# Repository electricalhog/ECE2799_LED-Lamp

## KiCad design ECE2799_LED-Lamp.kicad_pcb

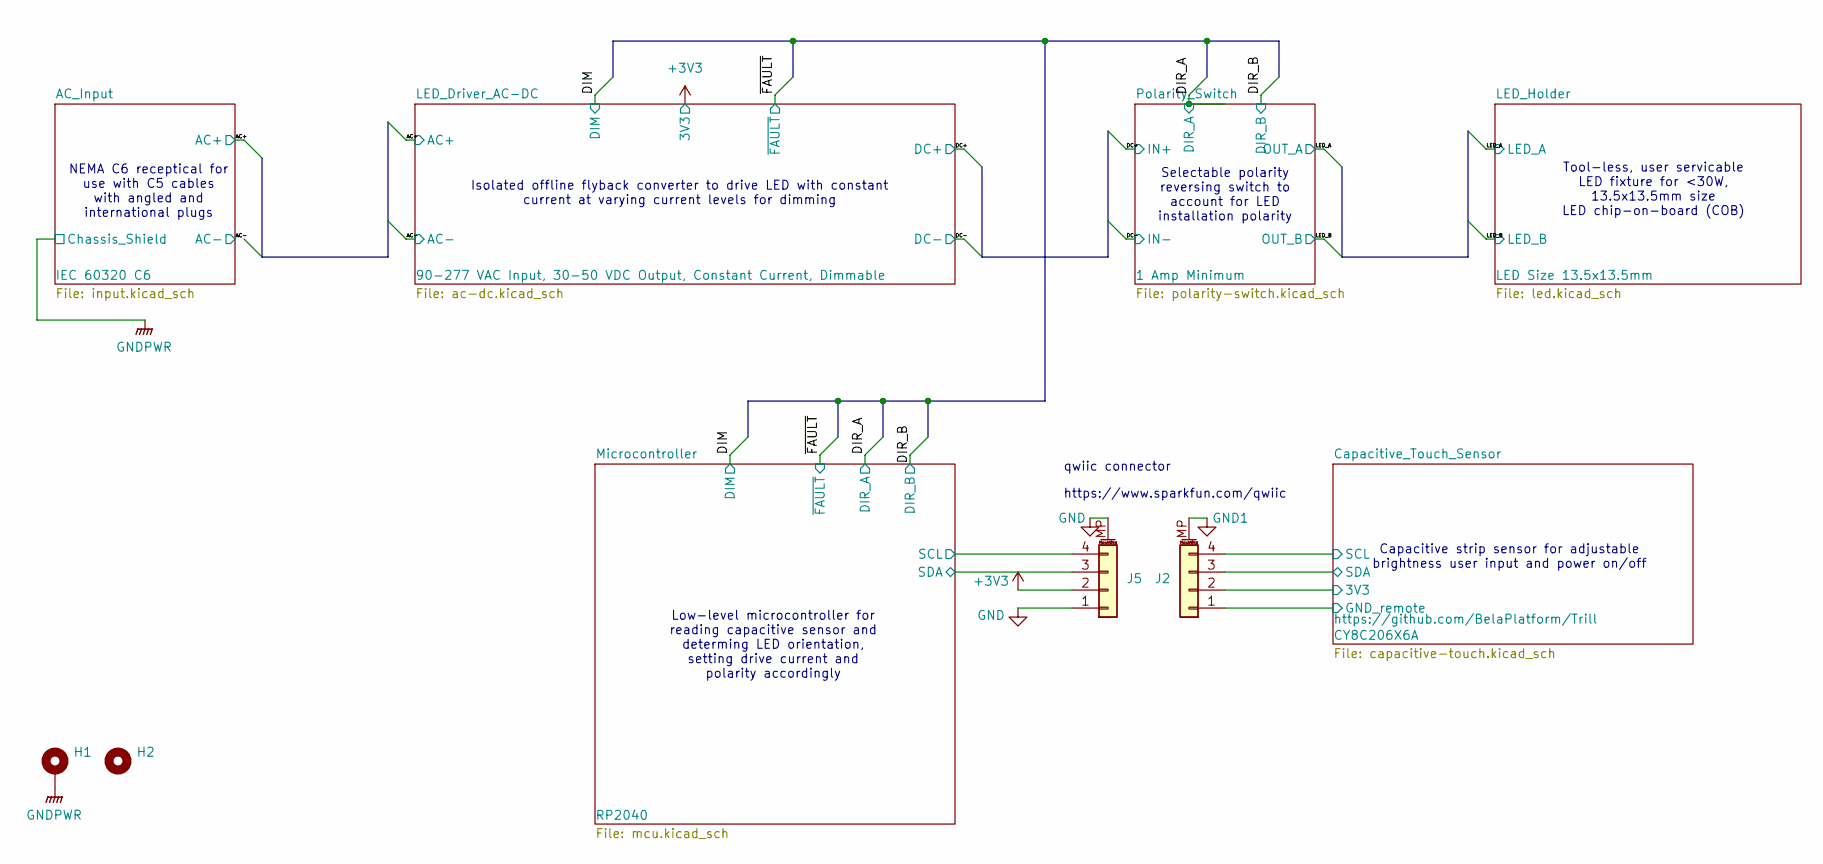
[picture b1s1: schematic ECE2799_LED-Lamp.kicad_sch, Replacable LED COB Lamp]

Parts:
H1: MountingHole_Pad; MountingHole_3.2mm_M3_Pad
H2: MountingHole; MountingHole_3.2mm_M3
J2, J5: Conn_01x04_MountingPin; qwiic_horizontal_SMD; Part Number PRT-14417-ND

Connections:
+3V3: J5.2; also elsewhere on the board
/Capacitive_Touch_Sensor/SCL: J2.4; also elsewhere on the board
/Capacitive_Touch_Sensor/SDA: J2.3; also elsewhere on the board
/Microcontroller/SCL: J5.4; also elsewhere on the board
/Microcontroller/SDA: J5.3; also elsewhere on the board
GND: J5.1, J5.MP (MountPin); also elsewhere on the board
GND1: J2.1, J2.MP (MountPin); also elsewhere on the board
GNDPWR: H1.1; also elsewhere on the board
VCC: J2.2; also elsewhere on the board

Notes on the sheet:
https://www.sparkfun.com/qwiic
NEMA C6 receptical for use with C5 cables with angled and international plugs
Isolated offline flyback converter to drive LED with constant current at varying current levels for dimming
Selectable polarity reversing switch to account for LED installation polarity
Tool-less, user servicable LED fixture for <30W, 13.5x13.5mm size LED chip-on-board (COB)
Low-level microcontroller for reading capacitive sensor and determing LED orientation, setting drive current and polarity accordingly
Capacitive strip sensor for adjustable brightness user input and power on/off
qwiic connector

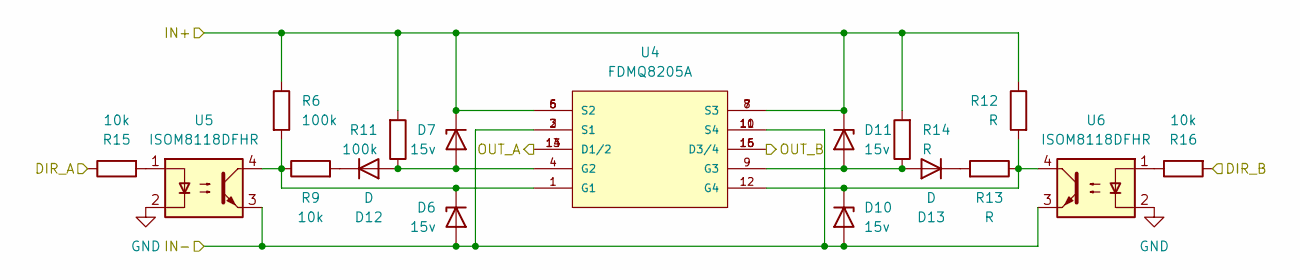
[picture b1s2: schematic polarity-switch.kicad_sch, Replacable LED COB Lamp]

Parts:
D6, D7, D10, D11: 15v; D_0603_1608Metric; Part Number 1727-6235-1-ND
D12, D13: D; D_0603_1608Metric; Part Number 1N4148WTDICT-ND
R6, R11: 100k; R_0603_1608Metric
R9, R15, R16: 10k; R_0603_1608Metric
R12, R13, R14: R; R_0603_1608Metric
U4: FDMQ8205A; IC_FDMQ8205A; PARTREV 1.0
U5, U6: ISOM8118DFHR; SOP-4_4.4x2.6mm_P1.27mm; Part Number 296-ISOM8118DFHRCT-ND

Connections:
/DC+: D7.1 (K), D11.1 (K), R6.1, R11.2, R12.1, R14.2, U4.5 (S2), U4.6 (S2), U4.7 (S3), U4.8 (S3); also elsewhere on the board
/DC-: D6.2 (A), D10.2 (A), U4.2 (S1), U4.3 (S1), U4.10 (S4), U4.11 (S4), U5.3, U6.3; also elsewhere on the board
/DIR_A: R15.1; also elsewhere on the board
/DIR_B: R16.2; also elsewhere on the board
/LED_A: U4.13 (D1/2), U4.14 (D1/2); also elsewhere on the board
/LED_B: U4.15 (D3/4), U4.16 (D3/4); also elsewhere on the board
GND: U5.2, U6.2; also elsewhere on the board
unnamed: D6.1 (K), R6.2, R9.1, U4.1 (G1), U5.4
unnamed: D10.1 (K), R12.2, R13.1, U4.12 (G4), U6.4
unnamed: D11.2 (A), D13.2 (A), R14.1, U4.9 (G3)
unnamed: D7.2 (A), D12.2 (A), R11.1, U4.4 (G2)
unnamed: D12.1 (K), R9.2
unnamed: D13.1 (K), R13.2
unnamed: R15.2, U5.1
unnamed: R16.1, U6.1

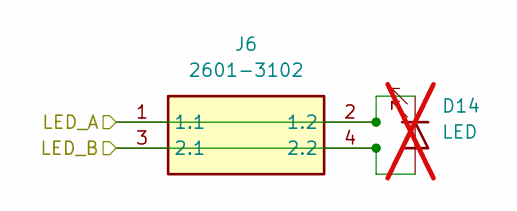
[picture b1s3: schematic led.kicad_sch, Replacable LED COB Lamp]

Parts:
D14: LED; Part Number 976-BXRH-40H1000-B-83-ND; not fitted
J6: 2601-3102; 26013102; Manufacturer_Part_Number 2601-3102

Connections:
/LED_A: D14.1 (K), J6.1 (1.1), J6.2 (1.2); also elsewhere on the board
/LED_B: D14.2 (A), J6.3 (2.1), J6.4 (2.2); also elsewhere on the board

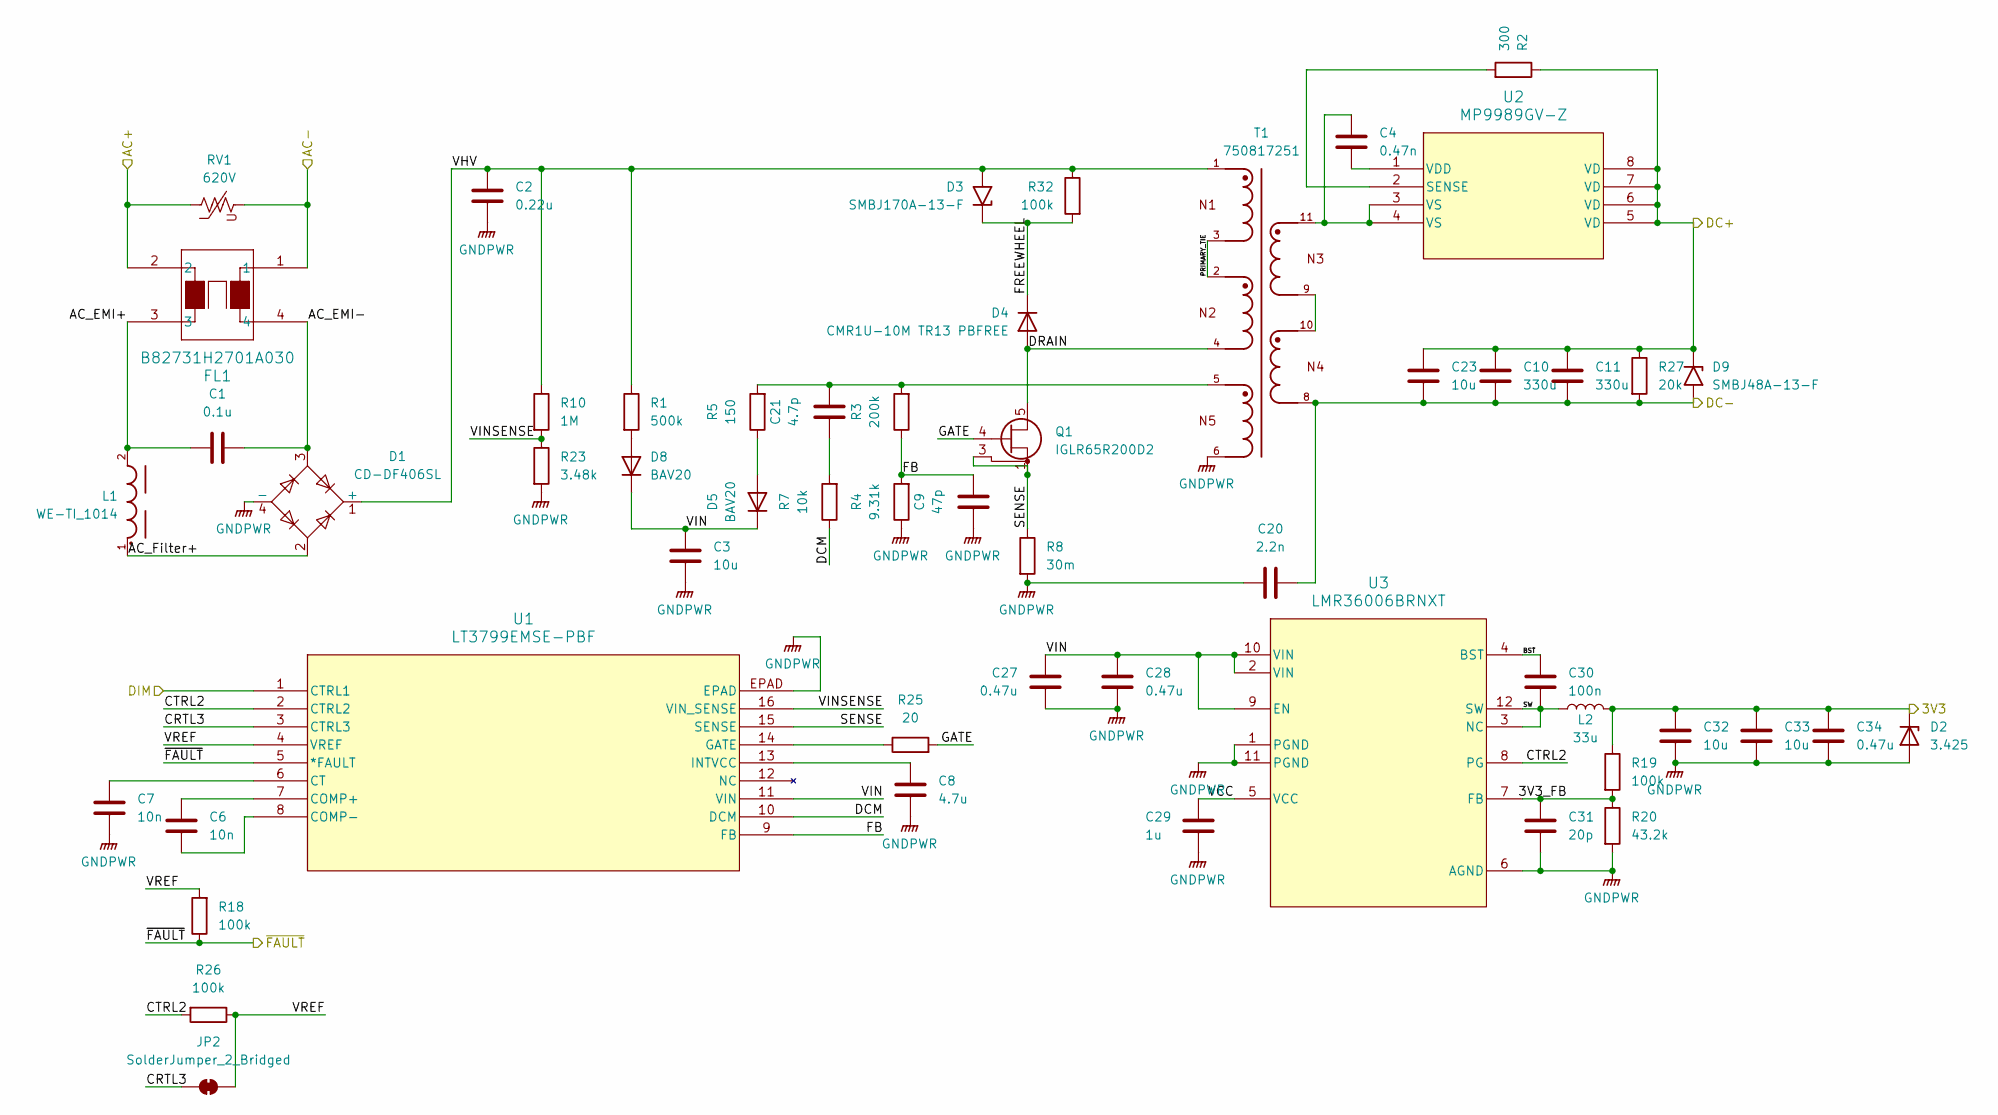
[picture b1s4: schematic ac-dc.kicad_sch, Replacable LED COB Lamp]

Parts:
C1: 0.1u; C_Rect_L13.0mm_W8.0mm_P10.00mm_FKS3_FKP3_MKS4; Part Number 732-5733-ND
C2: 0.22u; C_Rect_L18.0mm_W9.0mm_P15.00mm_FKS3_FKP3; Part Number 732-890414025003CS-ND
C3: 10u; CP_Radial_D5.0mm_P2.00mm; Part Number 732-9289-1-ND
C4: 0.47n; C_0603_1608Metric
C6, C7: 10n; C_0603_1608Metric
C8: 4.7u; C_0603_1608Metric
C9: 47p; C_0603_1608Metric
C10, C11: 330u; CP_Radial_D12.5mm_P5.00mm; Part Number UBT1J331MHD8-ND
C20: 2.2n; C_Disc_D11.0mm_W5.0mm_P10.00mm; Part Number BC3229-ND
C21: 4.7p; C_0603_1608Metric
C23, C32, C33: 10u; C_1206_3216Metric; Part Number 1276-6767-1-ND
C27, C28, C34: 0.47u; C_0805_2012Metric; Part Number 1276-6482-1-ND
C29: 1u; C_0603_1608Metric
C30: 100n; C_0603_1608Metric
C31: 20p; C_0603_1608Metric
D1: CD-DF406SL; Diode_Bridge_Bourns_CD-DF4xxS; Part Number 118-CD-DF406SLCT-ND
D2: 3.425; D_0603_1608Metric; Part Number 1727-8343-1-ND
D3: SMBJ170A-13-F; D_SMB; Part Number 31-SMBJ170A-13-FCT-ND
D4: CMR1U-10M TR13 PBFREE; D_SMA; Part Number 1514-CMR1U-10MTR13PBFREECT-ND
D5, D8: BAV20; D_SOD-123; Part Number BAV20W-FDICT-ND
D9: SMBJ48A-13-F; D_SMB; Part Number SMBJ48A-FDICT-ND
FL1: B82731H2701A030; B82731H_EPC; Part Number 495-5744-ND
JP2: SolderJumper_2_Bridged; SolderJumper-2_P1.3mm_Bridged2Bar_RoundedPad1.0x1.5mm
L1: WE-TI_1014; Part Number 732-4199-ND
L2: 33u; L_Wuerth_MAPI-3015; Part Number 732-4871-1-ND
Q1: IGLR65R200D2; PG-TSON-8-8; Part Number 448-IGLR65R200D2XUMA1CT-ND
R1: 500k; R_2010_5025Metric; Part Number 13-RC2010FK-07499KLCT-ND
R2: 300; R_0603_1608Metric
R3: 200k; R_0603_1608Metric
R4: 9.31k; R_0603_1608Metric
R5: 150; R_0603_1608Metric
R7: 10k; R_0603_1608Metric
R8: 30m; R_1206_3216Metric; Part Number WSLC-.03CT-ND
R10: 1M; R_1812_4532Metric; Part Number 10-ERJ-S12J105UCT-ND
R18, R19, R26: 100k; R_0603_1608Metric
R20: 43.2k; R_0603_1608Metric
R23: 3.48k; R_0603_1608Metric
R25: 20; R_0603_1608Metric
R27: 20k; R_1206_3216Metric; Part Number 541-4187-1-ND
R32: 100k; R_2010_5025Metric; Part Number 13-RC2010JK-07100KLCT-ND
RV1: 620V; RV_Disc_D12mm_W7.5mm_P7.5mm; Part Number 732-13263-1-ND
T1: 750817251; WE-OLLT_ER28_14_L31W31H25_PAD1.6; Part Number 1297-750817251-ND
U1: LT3799EMSE-PBF; MSOP-16_MSE_LIT; Part Number 505-LT3799EMSE#PBF-ND
U2: MP9989GV-Z; QFN-4x5_MP9989_MNP; Part Number 1589-MP9989GV-ZCT-ND
U3: LMR36006BRNXT; LMR36006; Part Number 296-53036-1-ND

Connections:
+3V3: C32.1, C33.1, C34.2, D2.1 (K), L2.2, R19.1; also elsewhere on the board
/AC+: FL1.2, RV1.1; also elsewhere on the board
/AC-: FL1.1, RV1.2; also elsewhere on the board
/DC+: C10.1, C11.1, C23.1, D9.1 (A1), R2.1, R27.1, U2.5 (VD), U2.6 (VD), U2.7 (VD), U2.8 (VD); also elsewhere on the board
/DC-: C10.2, C11.2, C20.2, C23.2, D9.2 (A2), R27.2, T1.8; also elsewhere on the board
/DIM: U1.1 (CTRL1); also elsewhere on the board
/LED_Driver_AC-DC/3V3_FB: C31.1, R19.2, R20.1, U3.7 (FB)
/LED_Driver_AC-DC/AC_EMI+: C1.1, FL1.3, L1.2
/LED_Driver_AC-DC/AC_EMI-: C1.2, D1.3, FL1.4
/LED_Driver_AC-DC/AC_Filter+: D1.2, L1.1
/LED_Driver_AC-DC/BST: C30.1, U3.4 (BST)
/LED_Driver_AC-DC/CRTL3: JP2.1 (A), U1.3 (CTRL3)
/LED_Driver_AC-DC/CTRL2: R26.2, U1.2 (CTRL2), U3.8 (PG)
/LED_Driver_AC-DC/DCM: R7.1, U1.10 (DCM)
/LED_Driver_AC-DC/DRAIN: D4.2 (A), Q1.5 (D), Q1.6 (D), Q1.7 (D), Q1.8 (D), T1.4
/LED_Driver_AC-DC/FB: C9.2, R3.1, R4.2, U1.9 (FB)
/LED_Driver_AC-DC/FREEWHEEL: D3.1 (A1), D4.1 (K), R32.2
/LED_Driver_AC-DC/GATE: Q1.4 (G), R25.2
/LED_Driver_AC-DC/PRIMARY_TIE: T1.2, T1.3
/LED_Driver_AC-DC/SENSE: Q1.1 (S), Q1.2 (S), Q1.3 (SS), Q1.9 (S), R8.1, U1.15 (SENSE)
/LED_Driver_AC-DC/SW: C30.2, L2.1, U3.3 (NC), U3.12 (SW)
/LED_Driver_AC-DC/VCC: C29.1, U3.5 (VCC)
/LED_Driver_AC-DC/VHV: C2.1, D1.1 (+), D3.2 (A2), R1.1, R10.1, R32.1, T1.1
/LED_Driver_AC-DC/VIN: C3.1, C27.2, C28.2, D5.1 (K), D8.1 (K), U1.11 (VIN), U3.2 (VIN), U3.9 (EN), U3.10 (VIN)
/LED_Driver_AC-DC/VINSENSE: R10.2, R23.1, U1.16 (VIN_SENSE)
/LED_Driver_AC-DC/VREF: JP2.2 (B), R18.2, R26.1, U1.4 (VREF)
/~FAULT: R18.1, U1.5 (*FAULT); also elsewhere on the board
GNDPWR: C2.2, C3.2, C7.2, C8.1, C9.1, C20.1, C27.1, C28.1, C29.2, C31.2, C32.2, C33.2, C34.1, D1.4 (-), D2.2 (A), R4.1, R8.2, R20.2, R23.2, T1.6, U1.EPAD, U3.1 (PGND), U3.6 (AGND), U3.11 (PGND); also elsewhere on the board
unnamed: C4.1, T1.11, U2.3 (VS), U2.4 (VS)
unnamed: C21.1, R7.2
unnamed: C21.2, R3.2, R5.2, T1.5
unnamed: D5.2 (A), R5.1
unnamed: D8.2 (A), R1.2
unnamed: T1.9, T1.10
unnamed: C6.1, U1.7 (COMP+)
unnamed: C6.2, U1.8 (COMP-)
unnamed: C7.1, U1.6 (CT)
unnamed: R25.1, U1.14 (GATE)
unnamed: C8.2, U1.13 (INTVCC)
unnamed: R2.2, U2.2 (SENSE)
unnamed: C4.2, U2.1 (VDD)

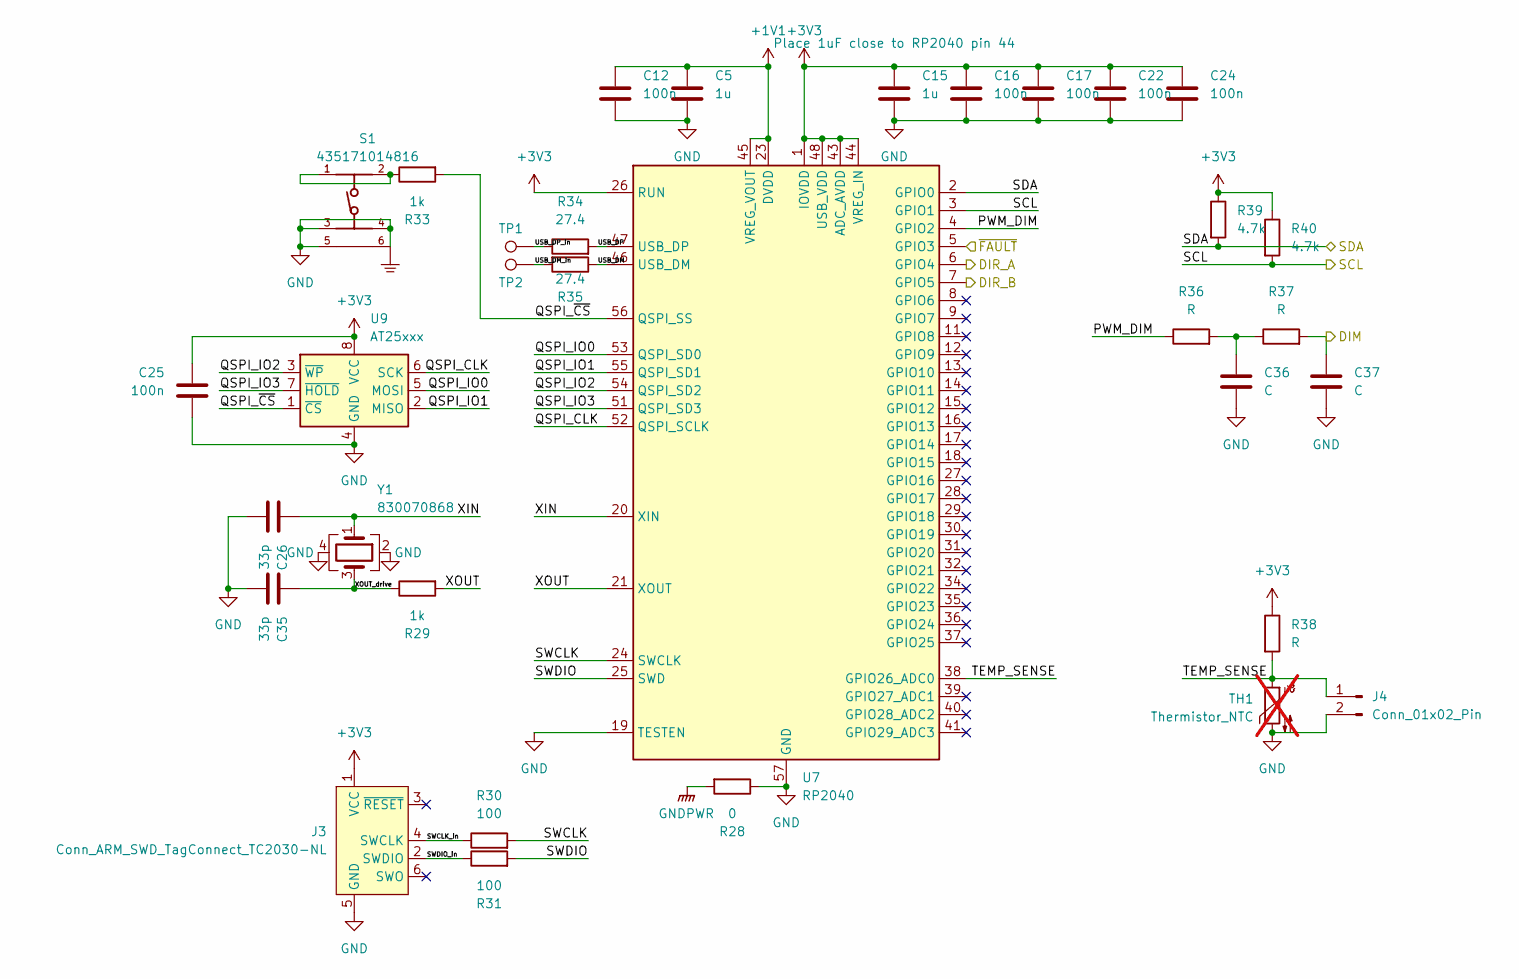
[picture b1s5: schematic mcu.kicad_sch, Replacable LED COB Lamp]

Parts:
C5, C15: 1u; C_0603_1608Metric
C12, C16, C17, C22, C24, C25: 100n; C_0603_1608Metric
C26, C35: 33p; C_0603_1608Metric
C36, C37: C; C_0603_1608Metric
J3: Conn_ARM_SWD_TagConnect_TC2030-NL; Tag-Connect_TC2030-IDC-NL_2x03_P1.27mm_Vertical
J4: Conn_01x02_Pin; PinHeader_1x02_P2.54mm_Vertical
R28: 0; R_0603_1608Metric
R29, R33: 1k; R_0603_1608Metric
R30, R31: 100; R_0603_1608Metric
R34, R35: 27.4; R_0603_1608Metric
R36, R37, R38: R; R_0603_1608Metric
R39, R40: 4.7k; R_0603_1608Metric
S1: 435171014816; Part Number P19889CT-ND
TH1: Thermistor_NTC; Part Number 56-NTCLP450E3104H-ND; not fitted
TP1, TP2: TestPoint; TestPoint_Pad_D2.0mm
U7: RP2040; QFN-56-1EP_7x7mm_P0.4mm_EP3.2x3.2mm; Part Number 2648-SC0914(13)CT-ND
U9: AT25xxx; SOIC-8_3.9x4.9mm_P1.27mm; Part Number 1265-AT25FF081A-SSHN-B-ND
Y1: 830070868; Crystal_SMD_3225-4Pin_3.2x2.5mm; Part Number 732-830070868CT-ND

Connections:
+1V1: C5.1, C12.1, U7.23 (DVDD), U7.45 (VREG_VOUT), U7.50 (DVDD)
+3V3: C15.1, C16.1, C17.1, C22.1, C24.1, C25.1, J3.1 (VCC), R38.1, R39.1, R40.1, U7.1 (IOVDD), U7.10 (IOVDD), U7.22 (IOVDD), U7.26 (RUN), U7.33 (IOVDD), U7.42 (IOVDD), U7.43 (ADC_AVDD), U7.44 (VREG_IN), U7.48 (USB_VDD), U7.49 (IOVDD), U9.8 (VCC); also elsewhere on the board
/DIM: C37.1, R37.2; also elsewhere on the board
/DIR_A: U7.6 (GPIO4); also elsewhere on the board
/DIR_B: U7.7 (GPIO5); also elsewhere on the board
/Microcontroller/PWM_DIM: R36.1, U7.4 (GPIO2)
/Microcontroller/QSPI_CLK: U7.52 (QSPI_SCLK), U9.6 (SCK)
/Microcontroller/QSPI_IO0: U7.53 (QSPI_SD0), U9.5 (MOSI)
/Microcontroller/QSPI_IO1: U7.55 (QSPI_SD1), U9.2 (MISO)
/Microcontroller/QSPI_IO2: U7.54 (QSPI_SD2), U9.3 (~WP)
/Microcontroller/QSPI_IO3: U7.51 (QSPI_SD3), U9.7 (~HOLD)
/Microcontroller/QSPI_~CS: R33.2, U7.56 (QSPI_SS), U9.1 (~CS)
/Microcontroller/SCL: R40.2, U7.3 (GPIO1); also elsewhere on the board
/Microcontroller/SDA: R39.2, U7.2 (GPIO0); also elsewhere on the board
/Microcontroller/SWCLK: R30.2, U7.24 (SWCLK)
/Microcontroller/SWCLK_in: J3.4 (SWCLK), R30.1
/Microcontroller/SWDIO: R31.2, U7.25 (SWD)
/Microcontroller/SWDIO_in: J3.2 (SWDIO), R31.1
/Microcontroller/TEMP_SENSE: J4.1, R38.2, TH1.1, U7.38 (GPIO26_ADC0)
/Microcontroller/USB_DM: R35.1, U7.46 (USB_DM)
/Microcontroller/USB_DM_in: R35.2, TP2.1
/Microcontroller/USB_DP: R34.2, U7.47 (USB_DP)
/Microcontroller/USB_DP_in: R34.1, TP1.1
/Microcontroller/XIN: C26.1, U7.20 (XIN), Y1.1
/Microcontroller/XOUT: R29.2, U7.21 (XOUT)
/Microcontroller/XOUT_drive: C35.1, R29.1, Y1.3
/~FAULT: U7.5 (GPIO3); also elsewhere on the board
GND: C5.2, C12.2, C15.2, C16.2, C17.2, C22.2, C24.2, C25.2, C26.2, C35.2, C36.2, C37.2, J3.5 (GND), J4.2, R28.1, S1.3, S1.4, S1.5, S1.6, TH1.2, U7.19 (TESTEN), U7.57 (GND), U9.4 (GND), Y1.2, Y1.4; also elsewhere on the board
GNDPWR: R28.2; also elsewhere on the board
unnamed: C36.1, R36.2, R37.1
unnamed: R33.1, S1.1, S1.2

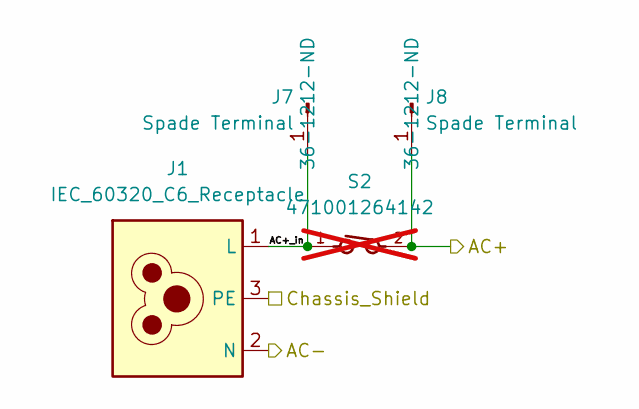
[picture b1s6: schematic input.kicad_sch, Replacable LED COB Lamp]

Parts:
J1: IEC_60320_C6_Receptacle; IEC_60320_C6; Part Number 486-4031-ND
J7, J8: Spade Terminal; 1212; Part Number 36-1212-ND
S2: 471001264142; 471001264142_0_75-1_25_; Part Number 732-13673-ND; not fitted

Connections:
/AC+: J8.1, S2.2; also elsewhere on the board
/AC-: J1.2 (N); also elsewhere on the board
/AC_Input/AC+_in: J1.1 (L), J7.1, S2.1
GNDPWR: J1.3 (PE); also elsewhere on the board

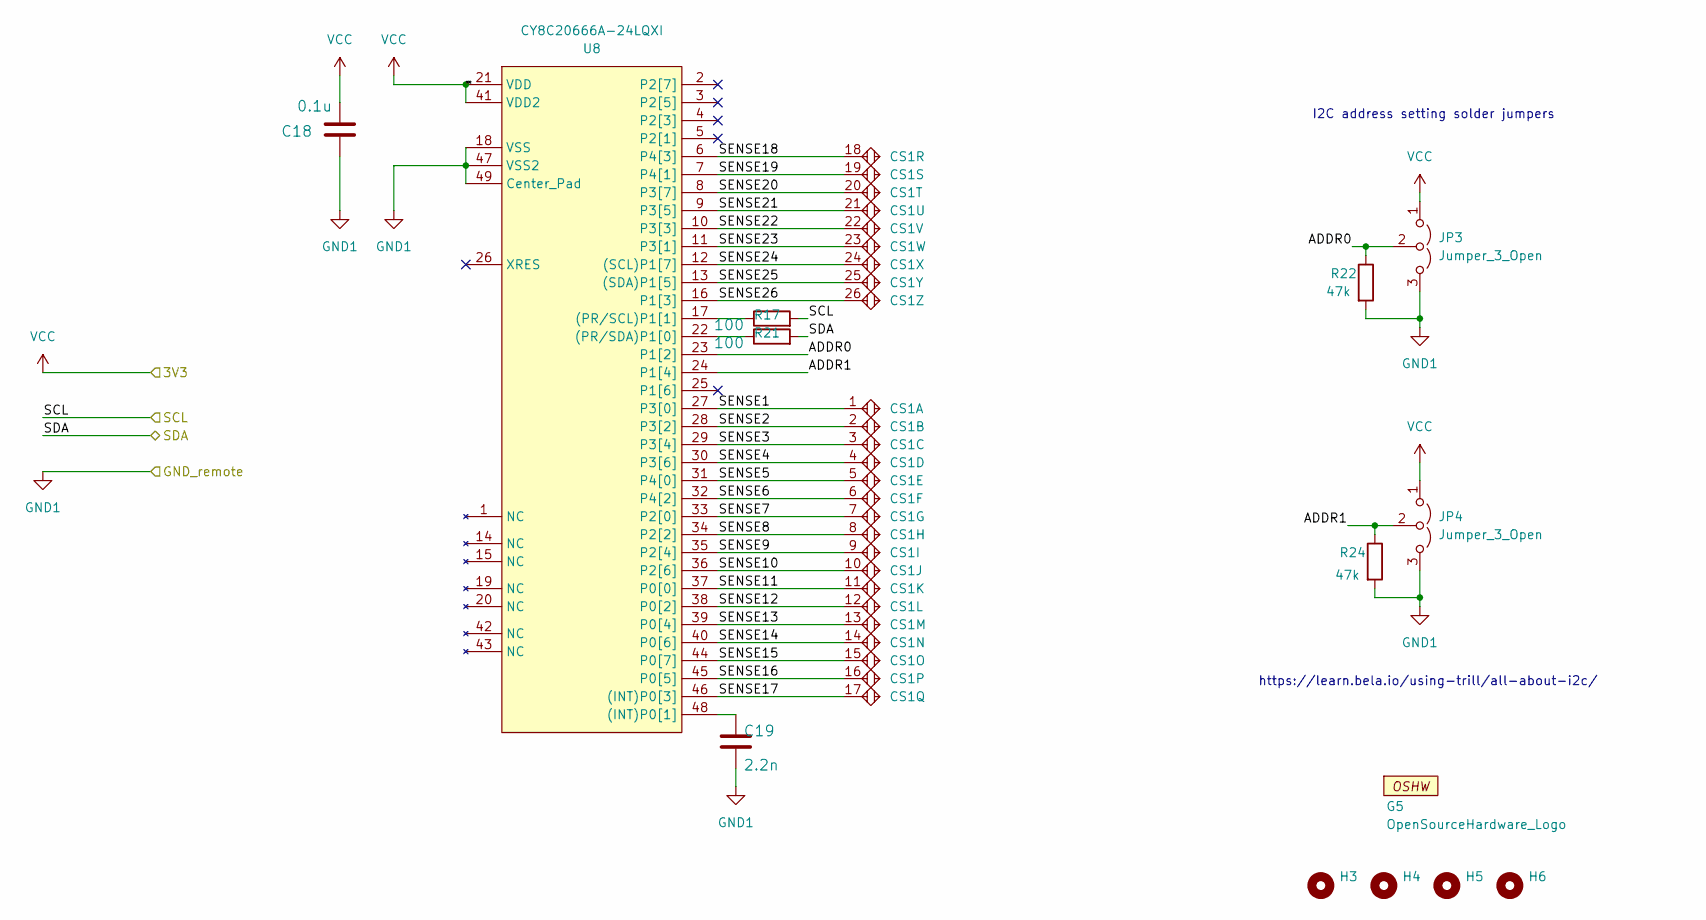
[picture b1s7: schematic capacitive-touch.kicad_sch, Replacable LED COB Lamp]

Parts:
C18: 0.1u; C_0603_1608Metric
C19: 2.2n; C_0603_1608Metric
CS1: TRILL_BAR-26_CapSense; TRILL_BAR_CapSense
G5: OpenSourceHardware_Logo
H3, H4, H5, H6: MountingHole; MountingHole_3.2mm_M3
JP3, JP4: Jumper_3_Open; SolderJumper-3_P1.3mm_Open_RoundedPad1.0x1.5mm
R17, R21: 100; R_0603_1608Metric
R22, R24: 47k; R_0603_1608Metric
U8: CY8C20666A-24LQXI; QFN-48-1EP_6x6mm_P0.4mm_EP4.6x4.6mm; Part Number 448-CY8C20646A-24LQXI-ND

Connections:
/Capacitive_Touch_Sensor/ADDR0: JP3.2 (C), R22.1, U8.23 (P1[2])
/Capacitive_Touch_Sensor/ADDR1: JP4.2 (C), R24.1, U8.24 (P1[4])
/Capacitive_Touch_Sensor/SCL: R17.2; also elsewhere on the board
/Capacitive_Touch_Sensor/SDA: R21.2; also elsewhere on the board
/Capacitive_Touch_Sensor/SENSE1: CS1.1, U8.27 (P3[0])
/Capacitive_Touch_Sensor/SENSE2: CS1.2, U8.28 (P3[2])
/Capacitive_Touch_Sensor/SENSE3: CS1.3, U8.29 (P3[4])
/Capacitive_Touch_Sensor/SENSE4: CS1.4, U8.30 (P3[6])
/Capacitive_Touch_Sensor/SENSE5: CS1.5, U8.31 (P4[0])
/Capacitive_Touch_Sensor/SENSE6: CS1.6, U8.32 (P4[2])
/Capacitive_Touch_Sensor/SENSE7: CS1.7, U8.33 (P2[0])
/Capacitive_Touch_Sensor/SENSE8: CS1.8, U8.34 (P2[2])
/Capacitive_Touch_Sensor/SENSE9: CS1.9, U8.35 (P2[4])
/Capacitive_Touch_Sensor/SENSE10: CS1.10, U8.36 (P2[6])
/Capacitive_Touch_Sensor/SENSE11: CS1.11, U8.37 (P0[0])
/Capacitive_Touch_Sensor/SENSE12: CS1.12, U8.38 (P0[2])
/Capacitive_Touch_Sensor/SENSE13: CS1.13, U8.39 (P0[4])
/Capacitive_Touch_Sensor/SENSE14: CS1.14, U8.40 (P0[6])
/Capacitive_Touch_Sensor/SENSE15: CS1.15, U8.44 (P0[7])
/Capacitive_Touch_Sensor/SENSE16: CS1.16, U8.45 (P0[5])
/Capacitive_Touch_Sensor/SENSE17: CS1.17, U8.46 ((INT)P0[3])
/Capacitive_Touch_Sensor/SENSE18: CS1.18, U8.6 (P4[3])
/Capacitive_Touch_Sensor/SENSE19: CS1.19, U8.7 (P4[1])
/Capacitive_Touch_Sensor/SENSE20: CS1.20, U8.8 (P3[7])
/Capacitive_Touch_Sensor/SENSE21: CS1.21, U8.9 (P3[5])
/Capacitive_Touch_Sensor/SENSE22: CS1.22, U8.10 (P3[3])
/Capacitive_Touch_Sensor/SENSE23: CS1.23, U8.11 (P3[1])
/Capacitive_Touch_Sensor/SENSE24: CS1.24, U8.12 ((SCL)P1[7])
/Capacitive_Touch_Sensor/SENSE25: CS1.25, U8.13 ((SDA)P1[5])
/Capacitive_Touch_Sensor/SENSE26: CS1.26, U8.16 (P1[3])
GND1: C18.1, C19.2, JP3.3 (B), JP4.3 (B), R22.2, R24.2, U8.18 (VSS), U8.47 (VSS2), U8.49 (Center_Pad); also elsewhere on the board
unnamed: C19.1, U8.48 ((INT)P0[1])
unnamed: R17.1, U8.17 ((PR/SCL)P1[1])
unnamed: R21.1, U8.22 ((PR/SDA)P1[0])
VCC: C18.2, JP3.1 (A), JP4.1 (A), U8.21 (VDD), U8.41 (VDD2); also elsewhere on the board

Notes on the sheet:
I2C address setting solder jumpers
https://learn.bela.io/using-trill/all-about-i2c/

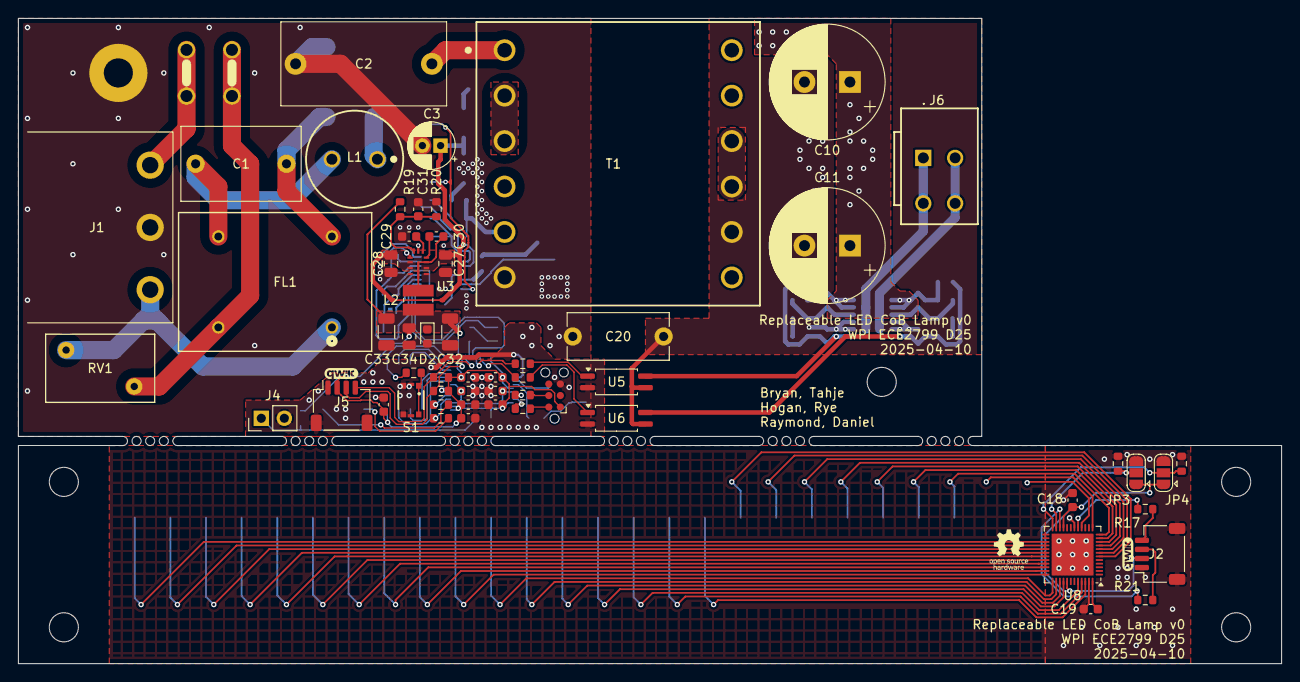
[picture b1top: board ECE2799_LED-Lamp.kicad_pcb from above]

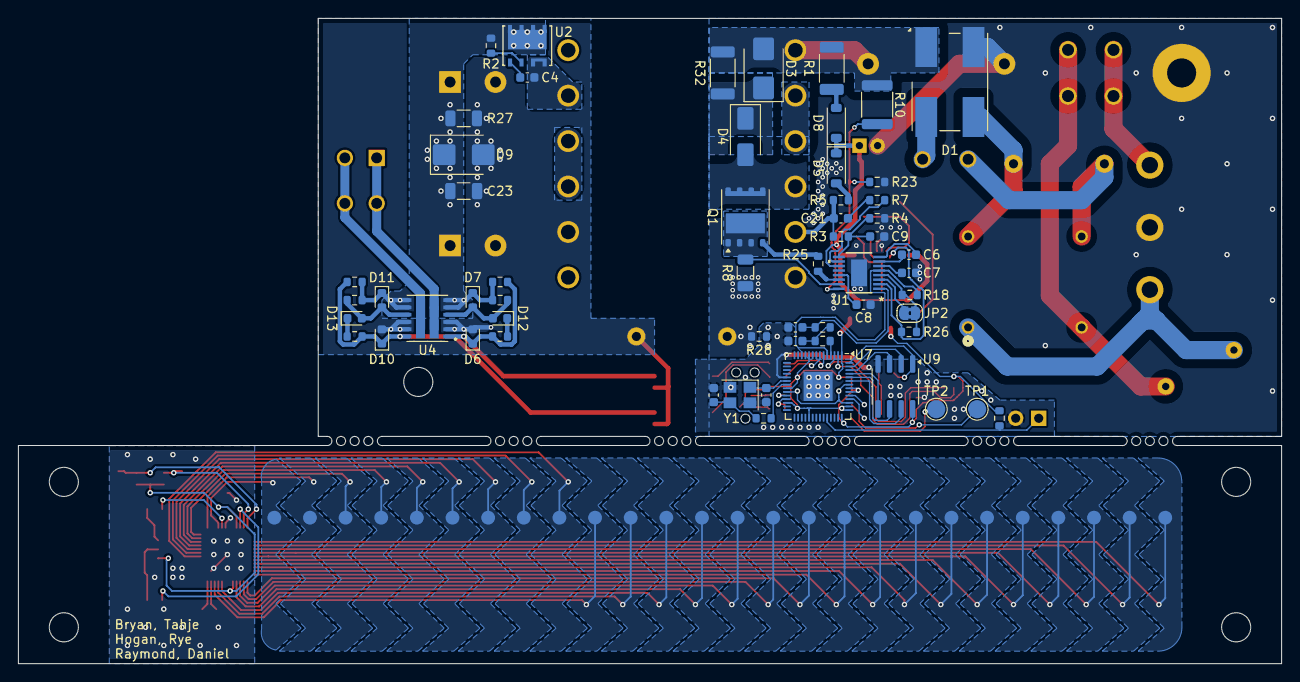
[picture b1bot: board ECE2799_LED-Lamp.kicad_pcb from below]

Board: 2 copper layers, 139.0 x 71.0 mm, 126 parts (58 on the bottom side), 114 nets.

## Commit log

2025-04-03 project init
2025-04-04 simulation
2025-04-05 new FET
2025-04-05 touch pcb
2025-04-08 updated components
    New ganfet selected and further work developing the rp2040 microcontroller circuit
2025-04-08 board routing progress
2025-04-08 Delete Simulation/Unloaded.txt
    Local simulation file too large to store in GitHub
2025-04-08 full layout
2025-04-08 updated pics
2025-04-09 finished board
2025-04-09 fabrication outputs
2025-04-10 production design files
2025-04-10 Updated Simulation
    Loaded GaN simulation model and updated schematic
2025-04-10 board interconnects
2025-04-10 pretty pictures
2025-04-17 Filter values
    Updated filter component values from lab experimentation
2025-04-18 sim and pdf
